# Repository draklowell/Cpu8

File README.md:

# Architecture of Dragonfly 8b9m CPU

## CPU4/4 (Made by previous students 2024)

## CPU8/16 (Made by students 2025)

## Google Spreadsheet for CPU components

<https://docs.google.com/spreadsheets/d/1K8h9GaudWlOMMR60cffy0GHXr_kNyvZ4bdUqfh8yQC4/edit?pli=1&gid=0#gid=0>

## Kicad Components and Footprints used in the project

### Bulk capacitor 100uF 16V

<https://www.rcscomponents.kiev.ua/product/100uf-16v-e5r-6-3x5mm-e5r101m16b-hitano-elektrolitychnyi-kondensator_14183.html>

**Footprint:**

Capacitor_THT:C_Radial_D6.3mm_H5.0mm_P2.50mm

### Decoupling capacitor 100nF 50V Y5V

<https://www.rcscomponents.kiev.ua/product/100nf-50v-y5v-k-10-d-5mm-cc-100n_163416.html>

**Footprints:**

Capacitor_THT:C_Disc_D5.0mm_W2.5mm_P5.00mm

Capacitor_THT:C_Disc_D5.0mm_W2.5mm_P2.50mm

### Resistor Pull UP 10k Ohm 0.25W

<https://www.rcscomponents.kiev.ua/product/10-kohm-5-0-25w-vyv-cr025sjtb-10k-hitano_13787.html>

**Footprint:**

Resistor_THT:R_Axial_DIN0207_L6.3mm_D2.5mm_P7

### Screw Terminal DG126/5.0-02P-14.00Z-H**

<https://www.rcscomponents.kiev.ua/product/klemnyk-dg126-5-0-02p-14-00z-h_18375.html>

**Footprint:**

<https://www.tme.eu/en/details/dg126-5.0-2p14/pcb-terminal-blocks/degson-electronics/dg126-5-0-02p-14-00a-h/>

### Connector PDB-38

<https://www.rcscomponents.kiev.ua/product/pbd-38-kls1-208-2-38-s_119543.html>

**Footprint:**

Connector_PinSocket_2.54mm:PinSocket_2x19_P2.54mm_Vertical

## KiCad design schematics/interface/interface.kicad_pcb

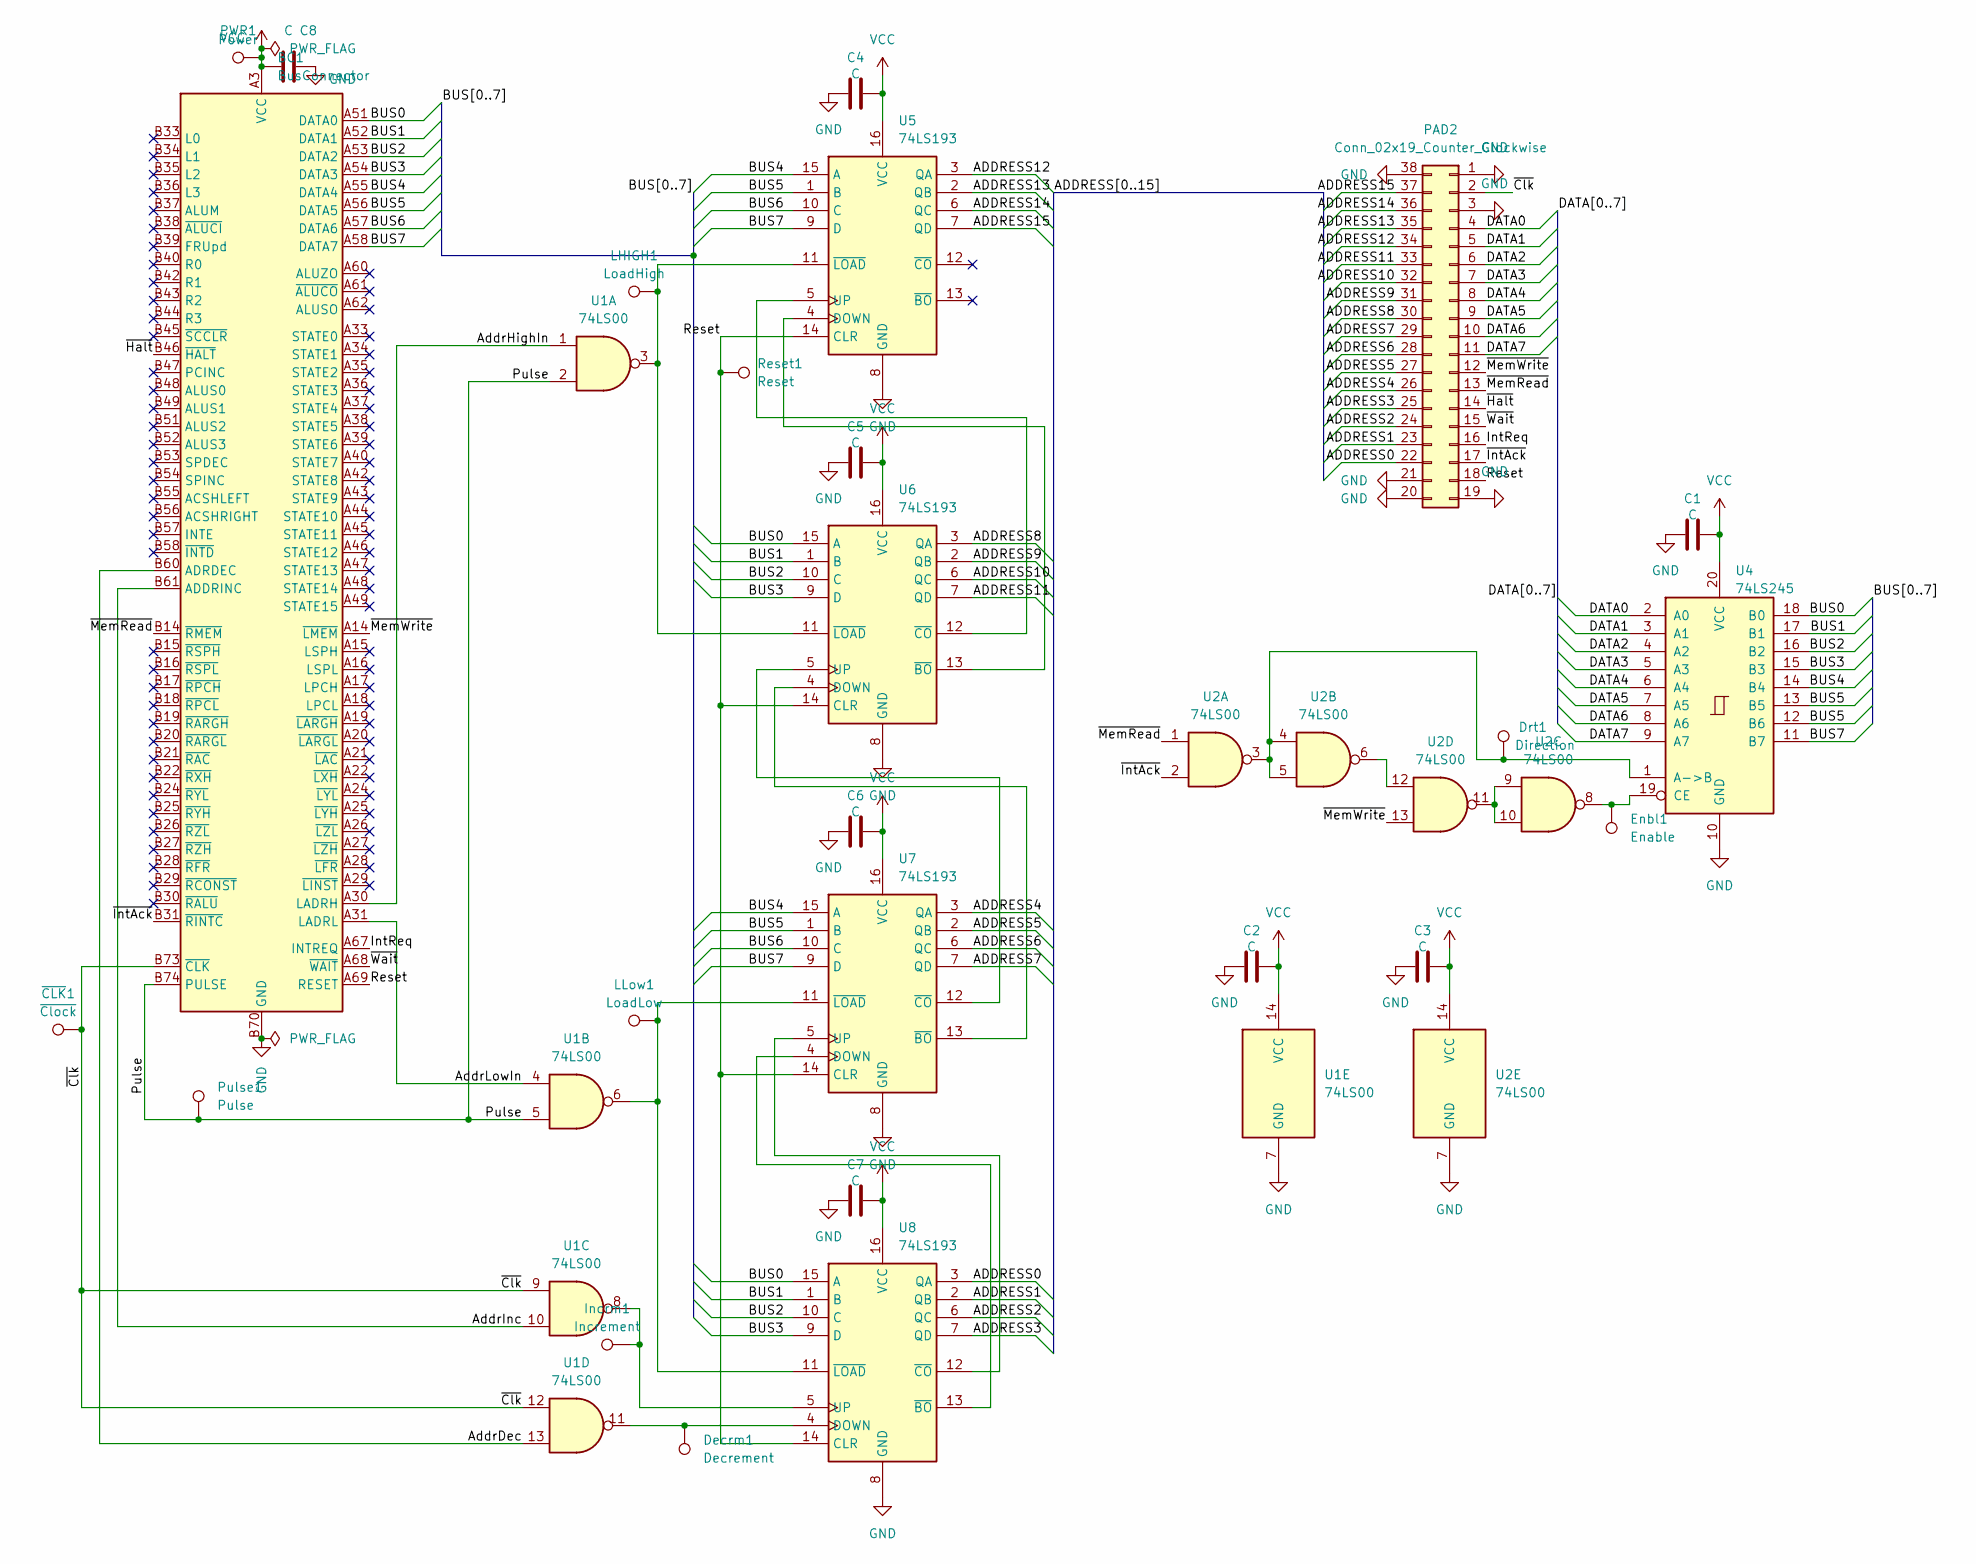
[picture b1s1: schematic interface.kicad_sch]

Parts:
BC1: BusConnector; BUS_PCIexpress_x16
C1, C2, C3, C4, C5, C6, C7: C; C_Disc_D5.0mm_W2.5mm_P5.00mm
C8: C; C_Radial_D6.3mm_H5.0mm_P2.50mm
Decrm1: Decrement; TestPoint_Pad_D1.0mm
Drt1: Direction; TestPoint_Pad_D1.0mm
Enbl1: Enable; TestPoint_Pad_D1.0mm
Incrm1: Increment; TestPoint_Pad_D1.0mm
LHIGH1: LoadHigh; TestPoint_Pad_D1.0mm
LLow1: LoadLow; TestPoint_Pad_D1.0mm
PAD2: Conn_02x19_Counter_Clockwise; PinSocket_2x19_P2.54mm_Vertical
PWR1: Power; TestPoint_Pad_D1.0mm
Pulse1: Pulse; TestPoint_Pad_D1.0mm
Reset1: Reset; TestPoint_Pad_D1.0mm
U1, U2: 74LS00; DIP-14_W7.62mm_Socket_LongPads
U4: 74LS245; DIP-20_W7.62mm_Socket_LongPads
U5, U6, U7, U8: 74LS193; DIP-16_W7.62mm_Socket_LongPads
~{CLK}1: ~{Clock}; TestPoint_Pad_D1.0mm

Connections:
/ADDRESS0: PAD2.22, U8.3 (QA)
/ADDRESS1: PAD2.23, U8.2 (QB)
/ADDRESS2: PAD2.24, U8.6 (QC)
/ADDRESS3: PAD2.25, U8.7 (QD)
/ADDRESS4: PAD2.26, U7.3 (QA)
/ADDRESS5: PAD2.27, U7.2 (QB)
/ADDRESS6: PAD2.28, U7.6 (QC)
/ADDRESS7: PAD2.29, U7.7 (QD)
/ADDRESS8: PAD2.30, U6.3 (QA)
/ADDRESS9: PAD2.31, U6.2 (QB)
/ADDRESS10: PAD2.32, U6.6 (QC)
/ADDRESS11: PAD2.33, U6.7 (QD)
/ADDRESS12: PAD2.34, U5.3 (QA)
/ADDRESS13: PAD2.35, U5.2 (QB)
/ADDRESS14: PAD2.36, U5.6 (QC)
/ADDRESS15: PAD2.37, U5.7 (QD)
/AddrDec: BC1.B60 (ADRDEC), U1.13
/AddrHighIn: BC1.A30 (LADRH), U1.1
/AddrInc: BC1.B61 (ADDRINC), U1.10
/AddrLowIn: BC1.A31 (LADRL), U1.4
/BUS0: BC1.A51 (DATA0), U4.18 (B0), U6.15 (A), U8.15 (A)
/BUS1: BC1.A52 (DATA1), U4.17 (B1), U6.1 (B), U8.1 (B)
/BUS2: BC1.A53 (DATA2), U4.16 (B2), U6.10 (C), U8.10 (C)
/BUS3: BC1.A54 (DATA3), U4.15 (B3), U6.9 (D), U8.9 (D)
/BUS4: BC1.A55 (DATA4), U4.14 (B4), U5.15 (A), U7.15 (A)
/BUS5: BC1.A56 (DATA5), U4.12 (B6), U4.13 (B5), U5.1 (B), U7.1 (B)
/BUS6: BC1.A57 (DATA6), U5.10 (C), U7.10 (C)
/BUS7: BC1.A58 (DATA7), U4.11 (B7), U5.9 (D), U7.9 (D)
/DATA0: PAD2.4, U4.2 (A0)
/DATA1: PAD2.5, U4.3 (A1)
/DATA2: PAD2.6, U4.4 (A2)
/DATA3: PAD2.7, U4.5 (A3)
/DATA4: PAD2.8, U4.6 (A4)
/DATA5: PAD2.9, U4.7 (A5)
/DATA6: PAD2.10, U4.8 (A6)
/DATA7: PAD2.11, U4.9 (A7)
/IntReq: BC1.A67 (INTREQ), PAD2.16
/Pulse: BC1.B74 (PULSE), Pulse1.1, U1.2, U1.5
/Reset: BC1.A69 (RESET), PAD2.18, Reset1.1, U5.14 (CLR), U6.14 (CLR), U7.14 (CLR), U8.14 (CLR)
/~Clk: BC1.B73 (~CLK), PAD2.2, U1.9, U1.12, ~{CLK}1.1
/~Halt: BC1.B46 (~HALT), PAD2.14
/~IntAck: BC1.B31 (~RINTC), PAD2.17, U2.2
/~MemRead: BC1.B14 (~RMEM), PAD2.13, U2.1
/~MemWrite: BC1.A14 (~LMEM), PAD2.12, U2.13
/~Wait: BC1.A68 (~WAIT), PAD2.15
GND: BC1.A12 (GND), BC1.A13 (GND), BC1.A23 (GND), BC1.A32 (GND), BC1.A41 (GND), BC1.A50 (GND), BC1.A59 (GND), BC1.A63 (GND), BC1.A64 (GND), BC1.A65 (GND), BC1.A66 (GND), BC1.A70 (GND), BC1.A71 (GND), BC1.A72 (GND), BC1.A73 (GND), BC1.A74 (GND), BC1.A75 (GND), BC1.A76 (GND), BC1.B12 (GND), BC1.B13 (GND), BC1.B23 (GND), BC1.B32 (GND), BC1.B41 (GND), BC1.B50 (GND), BC1.B59 (GND), BC1.B62 (GND), BC1.B63 (GND), BC1.B64 (GND), BC1.B65 (GND), BC1.B66 (GND), BC1.B67 (GND), BC1.B68 (GND), BC1.B69 (GND), BC1.B70 (GND), BC1.B71 (GND), BC1.B72 (GND), BC1.B75 (GND), BC1.B76 (GND), C1.2, C2.2, C3.2, C4.2, C5.2, C6.2, C7.2, C8.2, PAD2.1, PAD2.3, PAD2.19, PAD2.20, PAD2.21, PAD2.38, U1.7 (GND), U2.7 (GND), U4.10 (GND), U5.8 (GND), U6.8 (GND), U7.8 (GND), U8.8 (GND)
unnamed: U2.9, U2.10, U2.11
unnamed: U2.6, U2.12
unnamed: Drt1.1, U2.3, U2.4, U2.5, U4.1 (A->B)
unnamed: Enbl1.1, U2.8, U4.19 (CE)
unnamed: U5.4 (DOWN), U6.13 (~BO)
unnamed: U5.5 (UP), U6.12 (~CO)
unnamed: LHIGH1.1, U1.3, U5.11 (~LOAD), U6.11 (~LOAD)
unnamed: U6.4 (DOWN), U7.13 (~BO)
unnamed: U6.5 (UP), U7.12 (~CO)
unnamed: U7.4 (DOWN), U8.13 (~BO)
unnamed: U7.5 (UP), U8.12 (~CO)
unnamed: LLow1.1, U1.6, U7.11 (~LOAD), U8.11 (~LOAD)
unnamed: Decrm1.1, U1.11, U8.4 (DOWN)
unnamed: Incrm1.1, U1.8, U8.5 (UP)
VCC: BC1.A1 (VCC), BC1.A2 (VCC), BC1.A3 (VCC), BC1.A4 (VCC), BC1.A5 (VCC), BC1.B1 (VCC), BC1.B2 (VCC), BC1.B3 (VCC), BC1.B4 (VCC), BC1.B5 (VCC), C1.1, C2.1, C3.1, C4.1, C5.1, C6.1, C7.1, C8.1, PWR1.1, U1.14 (VCC), U2.14 (VCC), U4.20 (VCC), U5.16 (VCC), U6.16 (VCC), U7.16 (VCC), U8.16 (VCC)

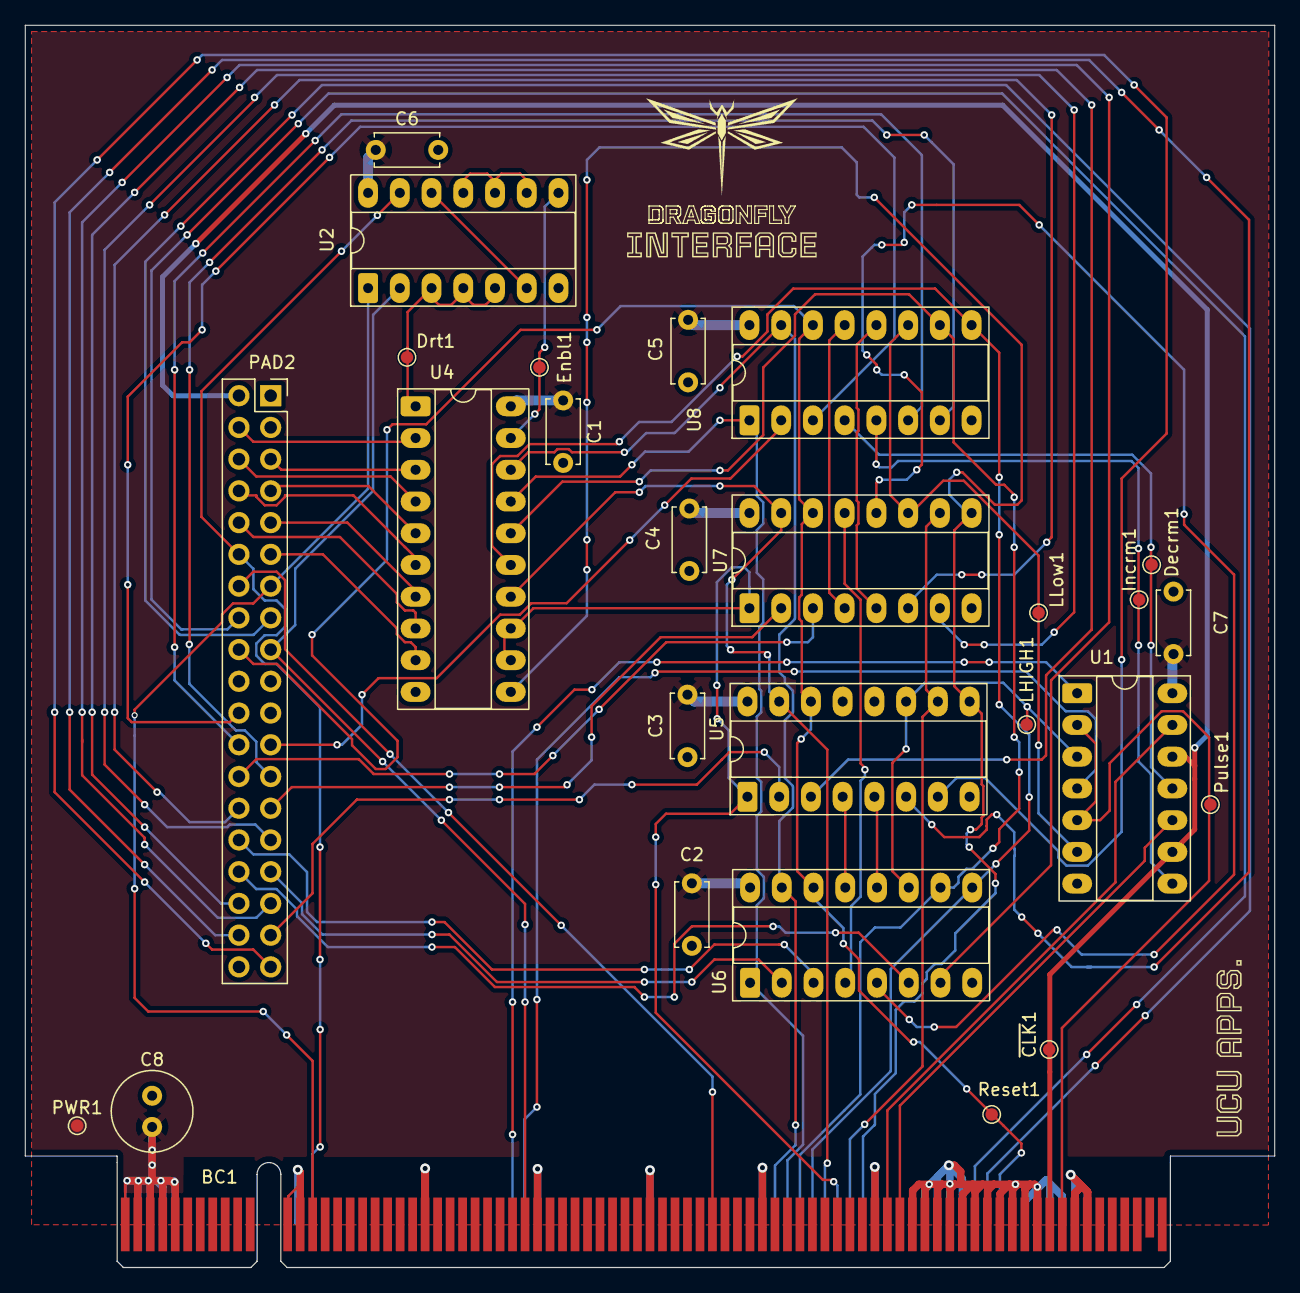
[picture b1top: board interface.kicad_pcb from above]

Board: 2 copper layers, 100.0 x 99.4 mm, 28 parts (0 on the bottom side), 61 nets.

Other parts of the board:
kibuzzard-691DE158: G***; kibuzzard-691DE158
kibuzzard-6911D1BC: G***; kibuzzard-6911D1BC

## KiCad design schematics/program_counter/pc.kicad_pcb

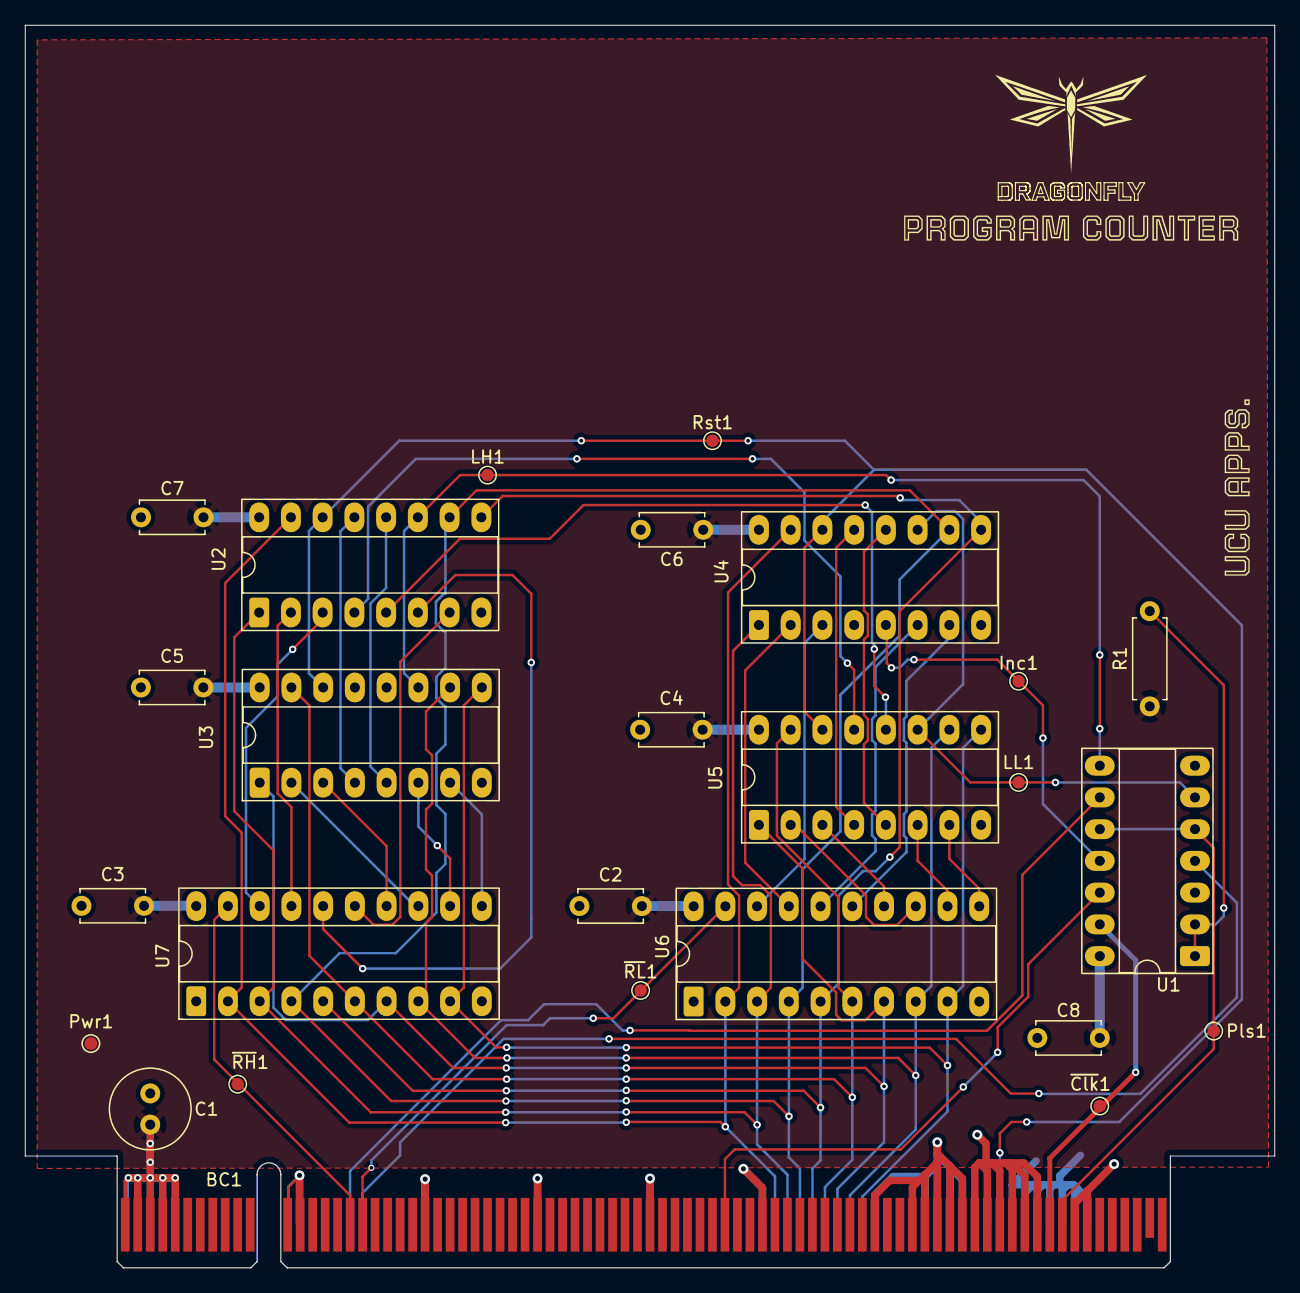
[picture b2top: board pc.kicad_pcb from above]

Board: 2 copper layers, 100.0 x 99.4 mm, 25 parts (0 on the bottom side), 44 nets.

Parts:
BC1: BusConnector; BUS_PCIexpress_x16
C1: C; C_Radial_D6.3mm_H5.0mm_P2.50mm
C2, C3, C4, C5, C6, C7, C8: C; C_Disc_D5.0mm_W2.5mm_P5.00mm
Inc1: Increment; TestPoint_Pad_D1.0mm
LH1: LoadHigh; TestPoint_Pad_D1.0mm
LL1: LoadLow; TestPoint_Pad_D1.0mm
Pls1: Pulse; TestPoint_Pad_D1.0mm
Pwr1: Power; TestPoint_Pad_D1.0mm
R1: R; R_Axial_DIN0207_L6.3mm_D2.5mm_P7.62mm_Horizontal
Rst1: Reset; TestPoint_Pad_D1.0mm
U1: 74HC00; DIP-14_W7.62mm_Socket_LongPads
U2, U3, U4, U5: 74HC193; DIP-16_W7.62mm_Socket_LongPads
U6, U7: 74HC245; DIP-20_W7.62mm_Socket_LongPads
kibuzzard-691DE17B: G***; kibuzzard-691DE17B
kibuzzard-6911BE41: G***; kibuzzard-6911BE41

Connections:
/CPu: Inc1.1, U1.11, U4.5 (UP)
/DATA0: BC1.A51 (DATA0), U2.15 (A), U4.15 (A), U6.2 (A0), U7.2 (A0)
/DATA1: BC1.A52 (DATA1), U2.1 (B), U4.1 (B), U6.3 (A1), U7.3 (A1)
/DATA2: BC1.A53 (DATA2), U2.10 (C), U4.10 (C), U6.4 (A2), U7.4 (A2)
/DATA3: BC1.A54 (DATA3), U2.9 (D), U4.9 (D), U6.5 (A3), U7.5 (A3)
/DATA4: BC1.A55 (DATA4), U3.15 (A), U5.15 (A), U6.6 (A4), U7.6 (A4)
/DATA5: BC1.A56 (DATA5), U3.1 (B), U5.1 (B), U6.7 (A5), U7.7 (A5)
/DATA6: BC1.A57 (DATA6), U3.10 (C), U5.10 (C), U6.8 (A6), U7.8 (A6)
/DATA7: BC1.A58 (DATA7), U3.9 (D), U5.9 (D), U6.9 (A7), U7.9 (A7)
/DH0: U2.3 (QA), U7.18 (B0)
/DH1: U2.2 (QB), U7.17 (B1)
/DH2: U2.6 (QC), U7.16 (B2)
/DH3: U2.7 (QD), U7.15 (B3)
/DH4: U3.3 (QA), U7.14 (B4)
/DH5: U3.2 (QB), U7.13 (B5)
/DH6: U3.6 (QC), U7.12 (B6)
/DH7: U3.7 (QD), U7.11 (B7)
/DL0: U4.3 (QA), U6.18 (B0)
/DL1: U4.2 (QB), U6.17 (B1)
/DL2: U4.6 (QC), U6.16 (B2)
/DL3: U4.7 (QD), U6.15 (B3)
/DL4: U5.3 (QA), U6.14 (B4)
/DL5: U5.2 (QB), U6.13 (B5)
/DL6: U5.6 (QC), U6.12 (B6)
/DL7: U5.7 (QD), U6.11 (B7)
/LPCH: BC1.A17 (LPCH), U1.9
/LPCL: BC1.A18 (LPCL), U1.4
/PCINC: BC1.B47 (PCINC), U1.12
/PULSE: BC1.B74 (PULSE), Pls1.1, U1.5, U1.10
/Ph: LH1.1, U1.8, U2.11 (~LOAD), U3.11 (~LOAD)
/Pl: LL1.1, U1.6, U4.11 (~LOAD), U5.11 (~LOAD)
/RESET: BC1.A69 (RESET), Rst1.1, U2.14 (CLR), U3.14 (CLR), U4.14 (CLR), U5.14 (CLR)
/~CLK: BC1.B73 (~CLK), U1.13
/~RPCH: BC1.B17 (~RPCH), U7.19 (CE)
/~RPCL: BC1.B18 (~RPCL), U6.19 (CE)
GND: BC1.A12 (GND), BC1.A13 (GND), BC1.A23 (GND), BC1.A32 (GND), BC1.A41 (GND), BC1.A50 (GND), BC1.A59 (GND), BC1.A63 (GND), BC1.A64 (GND), BC1.A65 (GND), BC1.A66 (GND), BC1.A70 (GND), BC1.A71 (GND), BC1.A72 (GND), BC1.A73 (GND), BC1.A74 (GND), BC1.A75 (GND), BC1.A76 (GND), BC1.B12 (GND), BC1.B13 (GND), BC1.B23 (GND), BC1.B32 (GND), BC1.B41 (GND), BC1.B50 (GND), BC1.B59 (GND), BC1.B62 (GND), BC1.B63 (GND), BC1.B64 (GND), BC1.B65 (GND), BC1.B66 (GND), BC1.B67 (GND), BC1.B68 (GND), BC1.B69 (GND), BC1.B70 (GND), BC1.B71 (GND), BC1.B72 (GND), BC1.B75 (GND), BC1.B76 (GND), C1.2, C2.1, C3.1, C4.1, C5.1, C6.1, C7.2, C8.2, U1.7 (GND), U2.8 (GND), U3.8 (GND), U4.8 (GND), U5.8 (GND), U6.1 (A->B), U6.10 (GND), U7.1 (A->B), U7.10 (GND)
unnamed: R1.2, U1.1, U1.2
unnamed: U2.4 (DOWN), U5.13 (~BO)
unnamed: U2.5 (UP), U5.12 (~CO)
unnamed: U2.13 (~BO), U3.4 (DOWN)
unnamed: U2.12 (~CO), U3.5 (UP)
unnamed: U4.13 (~BO), U5.4 (DOWN)
unnamed: U4.12 (~CO), U5.5 (UP)
VCC: BC1.A1 (VCC), BC1.A2 (VCC), BC1.A3 (VCC), BC1.A4 (VCC), BC1.A5 (VCC), BC1.B1 (VCC), BC1.B2 (VCC), BC1.B3 (VCC), BC1.B4 (VCC), BC1.B5 (VCC), C1.1, C2.2, C3.2, C4.2, C5.2, C6.2, C7.1, C8.1, Pwr1.1, R1.1, U1.14 (VCC), U2.16 (VCC), U3.16 (VCC), U4.16 (VCC), U5.16 (VCC), U6.20 (VCC), U7.20 (VCC)

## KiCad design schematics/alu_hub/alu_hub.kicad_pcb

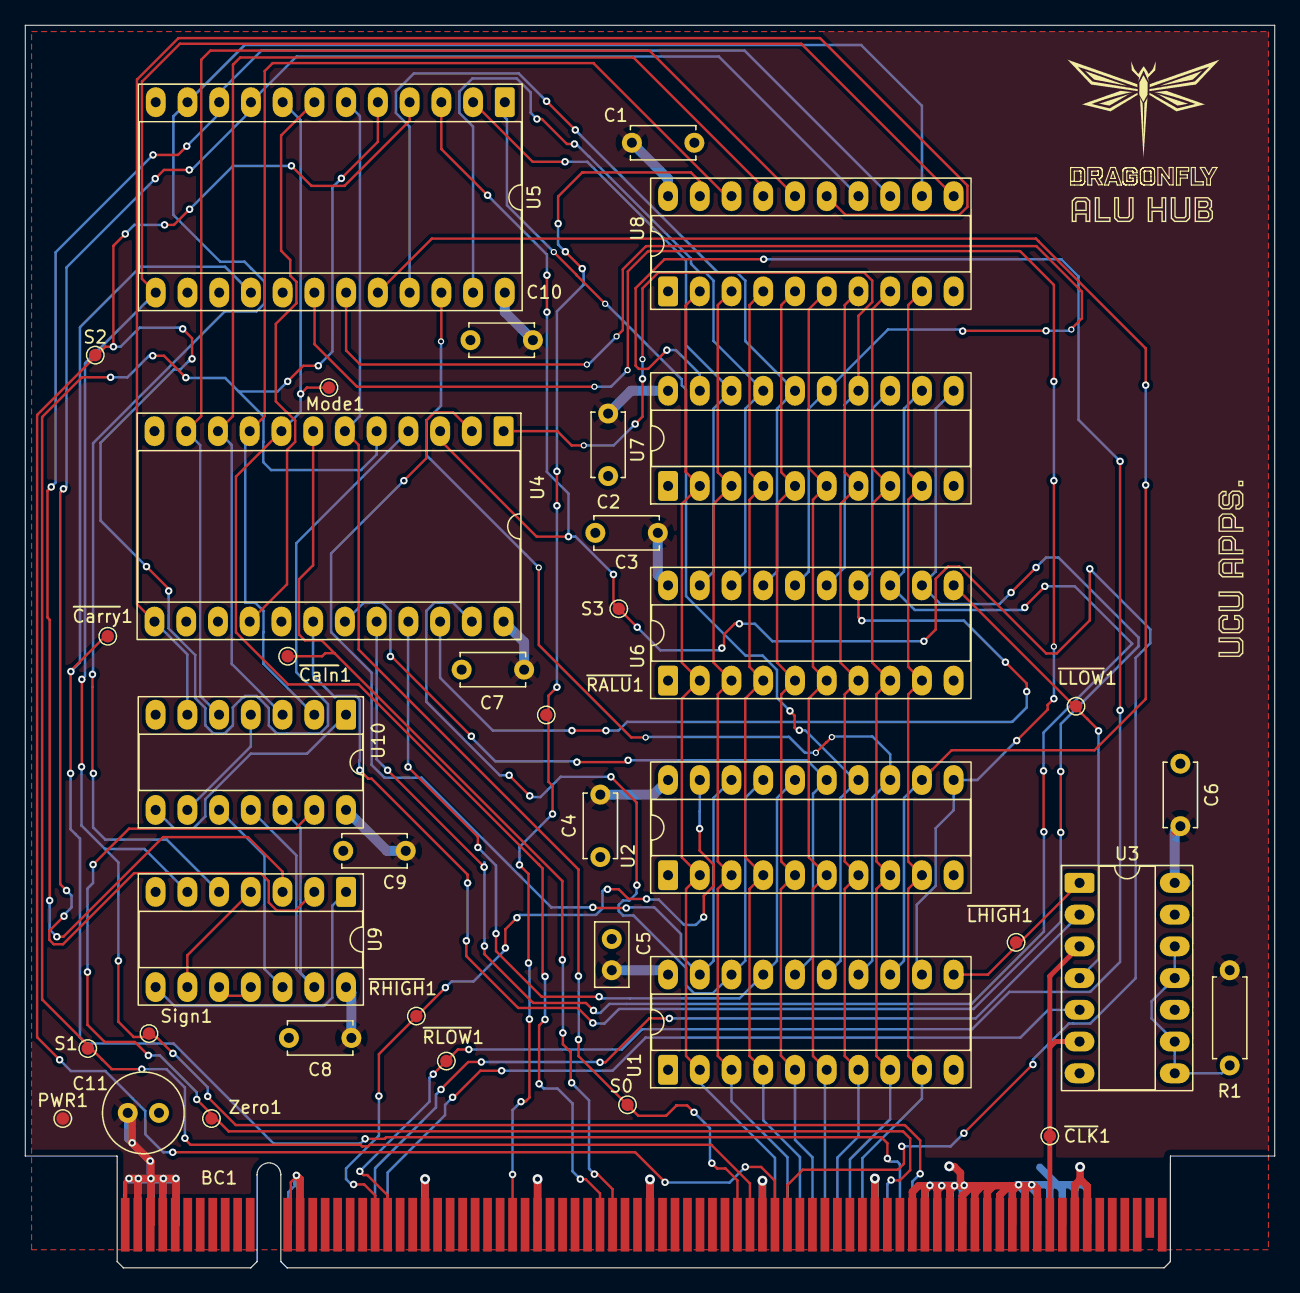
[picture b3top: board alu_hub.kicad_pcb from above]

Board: 2 copper layers, 100.0 x 99.4 mm, 33 parts (0 on the bottom side), 59 nets.

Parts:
BC1: BusConnector; BUS_PCIexpress_x16
C1, C2, C3, C4, C6, C7, C8, C9, C10: C; C_Disc_D5.0mm_W2.5mm_P5.00mm
C5: C; C_Disc_D5.0mm_W2.5mm_P2.50mm
C11: C; C_Radial_D6.3mm_H5.0mm_P2.50mm
Mode1: Mode; TestPoint_Pad_D1.0mm
PWR1: Power; TestPoint_Pad_D1.0mm
R1: R; R_Axial_DIN0207_L6.3mm_D2.5mm_P7.62mm_Horizontal
S0: S0; TestPoint_Pad_D1.0mm
S1: S1; TestPoint_Pad_D1.0mm
S2: S2; TestPoint_Pad_D1.0mm
S3: S3; TestPoint_Pad_D1.0mm
Sign1: Sign; TestPoint_Pad_D1.0mm
U1, U6: 74LS574; DIP-20_W7.62mm_Socket_LongPads
U2, U7, U8: 74LS245; DIP-20_W7.62mm_Socket_LongPads
U3, U9, U10: 74LS02; DIP-14_W7.62mm_Socket_LongPads
U4, U5: 74LS181; DIP-24_W15.24mm_Socket_LongPads
Zero1: Zero; TestPoint_Pad_D1.0mm
kibuzzard-691DDF7A: G***; kibuzzard-691DDF7A
kibuzzard-6911C7CA: G***; kibuzzard-6911C7CA

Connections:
/DATA0: BC1.A51 (DATA0), U1.2 (D0), U2.2 (A0), U6.2 (D0), U7.2 (A0), U8.2 (A0)
/DATA1: BC1.A52 (DATA1), U1.3 (D1), U2.3 (A1), U6.3 (D1), U7.3 (A1), U8.3 (A1)
/DATA2: BC1.A53 (DATA2), U1.4 (D2), U2.4 (A2), U6.4 (D2), U7.4 (A2), U8.4 (A2)
/DATA3: BC1.A54 (DATA3), U1.5 (D3), U2.5 (A3), U6.5 (D3), U7.5 (A3), U8.5 (A3)
/DATA4: BC1.A55 (DATA4), U1.6 (D4), U2.6 (A4), U6.6 (D4), U7.6 (A4), U8.6 (A4)
/DATA5: BC1.A56 (DATA5), U1.7 (D5), U2.7 (A5), U6.7 (D5), U7.7 (A5), U8.7 (A5)
/DATA6: BC1.A57 (DATA6), U1.8 (D6), U2.8 (A6), U6.8 (D6), U7.8 (A6), U8.8 (A6)
/DATA7: BC1.A58 (DATA7), U1.9 (D7), U2.9 (A7), U6.9 (D7), U7.9 (A7), U8.9 (A7)
/HIGH0: U1.19 (Q0), U2.18 (B0), U4.2 (A0)
/HIGH1: U1.18 (Q1), U2.17 (B1), U4.23 (A1)
/HIGH2: U1.17 (Q2), U2.16 (B2), U4.21 (A2)
/HIGH3: U1.16 (Q3), U2.15 (B3), U4.19 (A3)
/HIGH4: U1.15 (Q4), U2.14 (B4), U5.1 (B0)
/HIGH5: U1.14 (Q5), U2.13 (B5), U5.22 (B1)
/HIGH6: U1.13 (Q6), U2.12 (B6), U5.20 (B2)
/HIGH7: U1.12 (Q7), U2.11 (B7), U5.18 (B3)
/LOW0: U5.2 (A0), U6.19 (Q0), U7.18 (B0)
/LOW1: U5.23 (A1), U6.18 (Q1), U7.17 (B1)
/LOW2: U5.21 (A2), U6.17 (Q2), U7.16 (B2)
/LOW3: U5.19 (A3), U6.16 (Q3), U7.15 (B3)
/LOW4: U4.1 (B0), U6.15 (Q4), U7.14 (B4)
/LOW5: U4.22 (B1), U6.14 (Q5), U7.13 (B5)
/LOW6: U4.20 (B2), U6.13 (Q6), U7.12 (B6)
/LOW7: U4.18 (B3), U6.12 (Q7), U7.11 (B7)
GND: BC1.A12 (GND), BC1.A13 (GND), BC1.A23 (GND), BC1.A32 (GND), BC1.A41 (GND), BC1.A50 (GND), BC1.A59 (GND), BC1.A63 (GND), BC1.A64 (GND), BC1.A65 (GND), BC1.A66 (GND), BC1.A70 (GND), BC1.A71 (GND), BC1.A72 (GND), BC1.A73 (GND), BC1.A74 (GND), BC1.A75 (GND), BC1.A76 (GND), BC1.B12 (GND), BC1.B13 (GND), BC1.B23 (GND), BC1.B32 (GND), BC1.B41 (GND), BC1.B50 (GND), BC1.B59 (GND), BC1.B62 (GND), BC1.B63 (GND), BC1.B64 (GND), BC1.B65 (GND), BC1.B66 (GND), BC1.B67 (GND), BC1.B68 (GND), BC1.B69 (GND), BC1.B70 (GND), BC1.B71 (GND), BC1.B72 (GND), BC1.B75 (GND), BC1.B76 (GND), C1.1, C2.1, C3.1, C4.1, C5.1, C6.1, C7.1, C8.1, C9.1, C10.1, C11.1, U1.1 (OE), U1.10 (GND), U2.1 (A->B), U2.10 (GND), U3.7 (GND), U4.12 (GND), U5.12 (GND), U6.1 (OE), U6.10 (GND), U7.1 (A->B), U7.10 (GND), U8.1 (A->B), U8.10 (GND), U9.7 (GND), U10.7 (GND)
unnamed: BC1.B37 (ALUM), Mode1.1, U4.8 (M), U5.8 (M)
unnamed: BC1.B48 (ALUS0), S0.1, U4.6 (S0), U5.6 (S0)
unnamed: BC1.B49 (ALUS1), S1.1, U4.5 (S1), U5.5 (S1)
unnamed: BC1.B51 (ALUS2), S2.1, U4.4 (S2), U5.4 (S2)
unnamed: BC1.B52 (ALUS3), S3.1, U4.3 (S3), U5.3 (S3)
unnamed: BC1.A62 (ALUSO), Sign1.1, U5.13 (F3), U8.11 (B7), U9.6
unnamed: BC1.A60 (ALUZO), U10.13, Zero1.1
unnamed: BC1.B38 (~ALUCI), U4.7 (Cn)
unnamed: BC1.A61 (~ALUCO), U5.16 (Cn+4)
unnamed: BC1.B73 (~CLK), U3.3, U3.6
unnamed: BC1.A19 (~LARGH), U3.2
unnamed: BC1.A20 (~LARGL), U3.5
unnamed: BC1.B30 (~RALU), U8.19 (CE)
unnamed: BC1.B19 (~RARGH), U2.19 (CE)
unnamed: BC1.B20 (~RARGL), U7.19 (CE)
unnamed: R1.2, U3.8, U3.9, U3.11, U3.12
unnamed: U1.11 (Cp), U3.1
unnamed: U4.16 (Cn+4), U5.7 (Cn)
unnamed: U4.9 (F0), U8.18 (B0), U10.2
unnamed: U4.10 (F1), U8.17 (B1), U10.3
unnamed: U4.11 (F2), U8.16 (B2), U10.5
unnamed: U4.13 (F3), U8.15 (B3), U10.6
unnamed: U5.9 (F0), U8.14 (B4), U9.2
unnamed: U5.10 (F1), U8.13 (B5), U9.3
unnamed: U5.11 (F2), U8.12 (B6), U9.5
unnamed: U3.4, U6.11 (Cp)
unnamed: U9.1, U9.8
unnamed: U9.4, U9.9
unnamed: U9.10, U9.11
unnamed: U10.1, U10.8
unnamed: U10.4, U10.9
unnamed: U9.12, U10.10
unnamed: U9.13, U10.11, U10.12
VCC: BC1.A1 (VCC), BC1.A2 (VCC), BC1.A3 (VCC), BC1.A4 (VCC), BC1.A5 (VCC), BC1.B1 (VCC), BC1.B2 (VCC), BC1.B3 (VCC), BC1.B4 (VCC), BC1.B5 (VCC), C1.2, C2.2, C3.2, C4.2, C5.2, C6.2, C7.2, C8.2, C9.2, C10.2, C11.2, PWR1.1, R1.1, U1.20 (VCC), U2.20 (VCC), U3.14 (VCC), U4.24 (VCC), U5.24 (VCC), U6.20 (VCC), U7.20 (VCC), U8.20 (VCC), U9.14 (VCC), U10.14 (VCC)

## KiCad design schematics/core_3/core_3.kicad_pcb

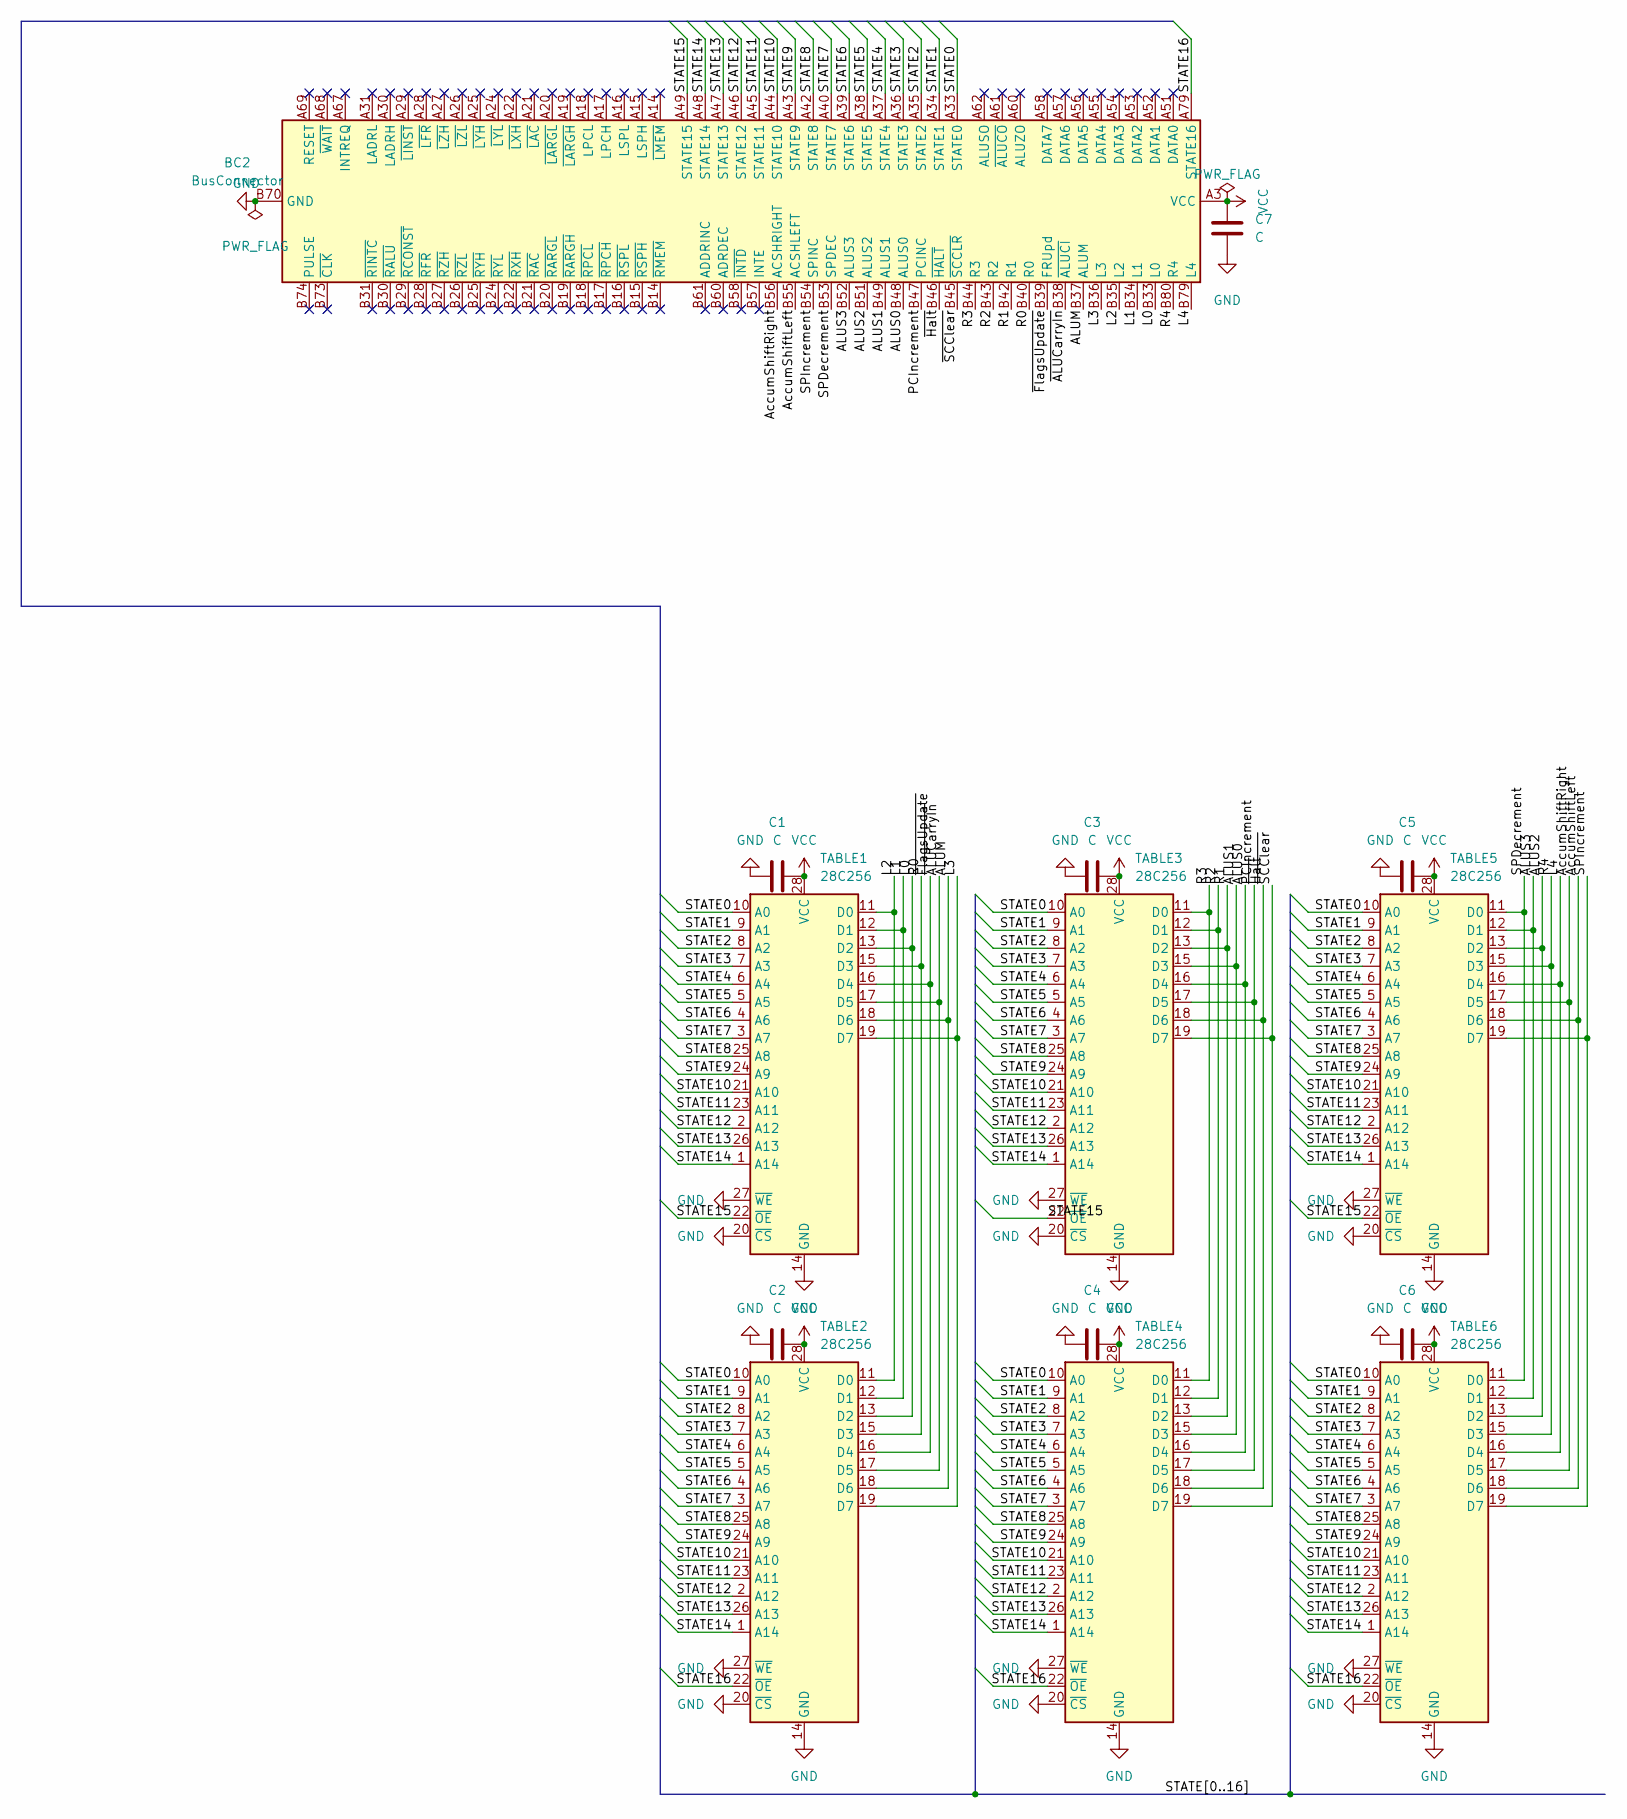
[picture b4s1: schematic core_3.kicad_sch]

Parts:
BC2: BusConnector; BUS_PCIexpress_x16
C1, C2, C3, C4, C5, C6: C; C_Disc_D5.0mm_W2.5mm_P2.50mm
C7: C; C_Radial_D6.3mm_H5.0mm_P2.50mm
TABLE1, TABLE2, TABLE3, TABLE4, TABLE5, TABLE6: 28C256; DIP-28_W15.24mm_Socket_LongPads

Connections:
/ALUM: BC2.B37 (ALUM), TABLE1.18 (D6), TABLE2.18 (D6)
/ALUS0: BC2.B48 (ALUS0), TABLE3.16 (D4), TABLE4.16 (D4)
/ALUS1: BC2.B49 (ALUS1), TABLE3.15 (D3), TABLE4.15 (D3)
/ALUS2: BC2.B51 (ALUS2), TABLE5.13 (D2), TABLE6.13 (D2)
/ALUS3: BC2.B52 (ALUS3), TABLE5.12 (D1), TABLE6.12 (D1)
/AccumShiftLeft: BC2.B55 (ACSHLEFT), TABLE5.18 (D6), TABLE6.18 (D6)
/AccumShiftRight: BC2.B56 (ACSHRIGHT), TABLE5.17 (D5), TABLE6.17 (D5)
/L0: BC2.B33 (L0), TABLE1.13 (D2), TABLE2.13 (D2)
/L1: BC2.B34 (L1), TABLE1.12 (D1), TABLE2.12 (D1)
/L2: BC2.B35 (L2), TABLE1.11 (D0), TABLE2.11 (D0)
/L3: BC2.B36 (L3), TABLE1.19 (D7), TABLE2.19 (D7)
/L4: BC2.B79 (L4), TABLE5.16 (D4), TABLE6.16 (D4)
/PCIncrement: BC2.B47 (PCINC), TABLE3.17 (D5), TABLE4.17 (D5)
/R0: BC2.B40 (R0), TABLE1.15 (D3), TABLE2.15 (D3)
/R1: BC2.B42 (R1), TABLE3.13 (D2), TABLE4.13 (D2)
/R2: BC2.B43 (R2), TABLE3.12 (D1), TABLE4.12 (D1)
/R3: BC2.B44 (R3), TABLE3.11 (D0), TABLE4.11 (D0)
/R4: BC2.B80 (R4), TABLE5.15 (D3), TABLE6.15 (D3)
/SPDecrement: BC2.B53 (SPDEC), TABLE5.11 (D0), TABLE6.11 (D0)
/SPIncrement: BC2.B54 (SPINC), TABLE5.19 (D7), TABLE6.19 (D7)
/STATE0: BC2.A33 (STATE0), TABLE1.10 (A0), TABLE2.10 (A0), TABLE3.10 (A0), TABLE4.10 (A0), TABLE5.10 (A0), TABLE6.10 (A0)
/STATE1: BC2.A34 (STATE1), TABLE1.9 (A1), TABLE2.9 (A1), TABLE3.9 (A1), TABLE4.9 (A1), TABLE5.9 (A1), TABLE6.9 (A1)
/STATE2: BC2.A35 (STATE2), TABLE1.8 (A2), TABLE2.8 (A2), TABLE3.8 (A2), TABLE4.8 (A2), TABLE5.8 (A2), TABLE6.8 (A2)
/STATE3: BC2.A36 (STATE3), TABLE1.7 (A3), TABLE2.7 (A3), TABLE3.7 (A3), TABLE4.7 (A3), TABLE5.7 (A3), TABLE6.7 (A3)
/STATE4: BC2.A37 (STATE4), TABLE1.6 (A4), TABLE2.6 (A4), TABLE3.6 (A4), TABLE4.6 (A4), TABLE5.6 (A4), TABLE6.6 (A4)
/STATE5: BC2.A38 (STATE5), TABLE1.5 (A5), TABLE2.5 (A5), TABLE3.5 (A5), TABLE4.5 (A5), TABLE5.5 (A5), TABLE6.5 (A5)
/STATE6: BC2.A39 (STATE6), TABLE1.4 (A6), TABLE2.4 (A6), TABLE3.4 (A6), TABLE4.4 (A6), TABLE5.4 (A6), TABLE6.4 (A6)
/STATE7: BC2.A40 (STATE7), TABLE1.3 (A7), TABLE2.3 (A7), TABLE3.3 (A7), TABLE4.3 (A7), TABLE5.3 (A7), TABLE6.3 (A7)
/STATE8: BC2.A42 (STATE8), TABLE1.25 (A8), TABLE2.25 (A8), TABLE3.25 (A8), TABLE4.25 (A8), TABLE5.25 (A8), TABLE6.25 (A8)
/STATE9: BC2.A43 (STATE9), TABLE1.24 (A9), TABLE2.24 (A9), TABLE3.24 (A9), TABLE4.24 (A9), TABLE5.24 (A9), TABLE6.24 (A9)
/STATE10: BC2.A44 (STATE10), TABLE1.21 (A10), TABLE2.21 (A10), TABLE3.21 (A10), TABLE4.21 (A10), TABLE5.21 (A10), TABLE6.21 (A10)
/STATE11: BC2.A45 (STATE11), TABLE1.23 (A11), TABLE2.23 (A11), TABLE3.23 (A11), TABLE4.23 (A11), TABLE5.23 (A11), TABLE6.23 (A11)
/STATE12: BC2.A46 (STATE12), TABLE1.2 (A12), TABLE2.2 (A12), TABLE3.2 (A12), TABLE4.2 (A12), TABLE5.2 (A12), TABLE6.2 (A12)
/STATE13: BC2.A47 (STATE13), TABLE1.26 (A13), TABLE2.26 (A13), TABLE3.26 (A13), TABLE4.26 (A13), TABLE5.26 (A13), TABLE6.26 (A13)
/STATE14: BC2.A48 (STATE14), TABLE1.1 (A14), TABLE2.1 (A14), TABLE3.1 (A14), TABLE4.1 (A14), TABLE5.1 (A14), TABLE6.1 (A14)
/STATE15: BC2.A49 (STATE15), TABLE1.22 (~OE), TABLE3.22 (~OE), TABLE5.22 (~OE)
/STATE16: BC2.A79 (STATE16), TABLE2.22 (~OE), TABLE4.22 (~OE), TABLE6.22 (~OE)
/~ALUCarryIn: BC2.B38 (~ALUCI), TABLE1.17 (D5), TABLE2.17 (D5)
/~FlagsUpdate: BC2.B39 (FRUpd), TABLE1.16 (D4), TABLE2.16 (D4)
/~Halt: BC2.B46 (~HALT), TABLE3.18 (D6), TABLE4.18 (D6)
/~SCClear: BC2.B45 (~SCCLR), TABLE3.19 (D7), TABLE4.19 (D7)
GND: BC2.A12 (GND), BC2.A13 (GND), BC2.A23 (GND), BC2.A32 (GND), BC2.A50 (GND), BC2.A59 (GND), BC2.A63 (GND), BC2.A64 (GND), BC2.A65 (GND), BC2.A66 (GND), BC2.A70 (GND), BC2.A71 (GND), BC2.A72 (GND), BC2.A73 (GND), BC2.A74 (GND), BC2.A75 (GND), BC2.A76 (GND), BC2.B12 (GND), BC2.B13 (GND), BC2.B23 (GND), BC2.B32 (GND), BC2.B50 (GND), BC2.B59 (GND), BC2.B62 (GND), BC2.B63 (GND), BC2.B64 (GND), BC2.B65 (GND), BC2.B66 (GND), BC2.B67 (GND), BC2.B68 (GND), BC2.B69 (GND), BC2.B70 (GND), BC2.B71 (GND), BC2.B72 (GND), BC2.B75 (GND), BC2.B76 (GND), C1.2, C2.2, C3.2, C4.2, C5.2, C6.2, C7.2, TABLE1.14 (GND), TABLE1.20 (~CS), TABLE1.27 (~WE), TABLE2.14 (GND), TABLE2.20 (~CS), TABLE2.27 (~WE), TABLE3.14 (GND), TABLE3.20 (~CS), TABLE3.27 (~WE), TABLE4.14 (GND), TABLE4.20 (~CS), TABLE4.27 (~WE), TABLE5.14 (GND), TABLE5.20 (~CS), TABLE5.27 (~WE), TABLE6.14 (GND), TABLE6.20 (~CS), TABLE6.27 (~WE)
VCC: BC2.A1 (VCC), BC2.A2 (VCC), BC2.A3 (VCC), BC2.A4 (VCC), BC2.A5 (VCC), BC2.B1 (VCC), BC2.B2 (VCC), BC2.B3 (VCC), BC2.B4 (VCC), BC2.B5 (VCC), C1.1, C2.1, C3.1, C4.1, C5.1, C6.1, C7.1, TABLE1.28 (VCC), TABLE2.28 (VCC), TABLE3.28 (VCC), TABLE4.28 (VCC), TABLE5.28 (VCC), TABLE6.28 (VCC)
